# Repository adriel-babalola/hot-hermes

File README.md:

# Hot Hermes 🌡️

a mini temperature sensor + display for environment and room temperatures, with a buzzer that warns me when it gets above 34°C so i dont burn my food while cooking lol.

## Why i made this

i cook a lot and my kitchen gets HOT. i wanted something small that could just sit there, show me the temperature, and scream at me (well, buzz loudly) when things get too warm. also i wanted to finally learn how I2C works and this was the perfect excuse.

## How it works

- **AHT20 module** reads the temperature and humidity over I2C
- **1.3" OLED** displays the readings in real time
- **Passive buzzer** goes off when temp hits above 34°C
- everything runs on the **XIAO RP2040**
- Then there's a case, in which everything is enclosed in
## Screenshots

> 

## BOM

| Item # | Designator | Description | Qty | Unit Price (USD) | Total + Shipping (USD) | Source | Link |
|--------|------------|-------------|-----|-----------------|----------------------|--------|------|
| 1 | U1 | Seeed XIAO RP2040 Microcontroller | 1 | $7.84 | $7.84 | AliExpress | [link](https://www.aliexpress.com/item/1005006593701624.html?spm=a2g0o.cart.0.0.742b38daUU8kz0&mp=1&pdp_npi=6%40dis%21USD%21USD+6.31%21USD+4.61%21%21USD+4.61%21%21%21%40211b876717768556104776423e1131%2112000039072595754%21ct%21NG%216438462769%21%211%210%21&pdp_ext_f=%7B%22cart2PdpParams%22%3A%7B%22pdpBusinessMode%22%3A%22retail%22%7D%7D) |
| 2 | DS1 | 1.3" I2C OLED Display Module 128x64 (Blue) | 1 | $2.83| $2.83 | AliExpress | [link](https://www.aliexpress.com/item/1005010183965559.html?spm=a2g0o.cart.0.0.742b38daUU8kz0&mp=1&pdp_npi=6%40dis%21USD%21USD+8.28%21USD+3.89%21%21USD+3.85%21%21%21%40211b876717768556104776423e1131%2112000051437252682%21ct%21NG%216438462769%21%211%210%21) |
| 3 | U2 | AHT20 Temperature & Humidity Sensor Module | 1 | $2.06 | $2.06 | AliExpress | [link](https://www.aliexpress.com/item/1005006088708984.html?spm=a2g0o.cart.0.0.742b38daUU8kz0&mp=1&pdp_npi=6%40dis%21USD%21USD+2.16%21USD+2.16%21%21USD+2.12%21%21%21%40211b876717768556104776423e1131%2112000035679578526%21ct%21NG%216438462769%21%211%210%21) 
| 5 | PCB | hermes_Y5 Custom PCB — 5pcs, JLCPCB | 1 | $5.00 | $11.92 | PCBWAY | [link](https://pcbway.com) |
|6| 3D Printing | The Case for Hot Hermes | 1 | 0 | $9.39  | #printing-legion hackclub | - |
| | | | | **TOTAL** | **$34.02** | | |

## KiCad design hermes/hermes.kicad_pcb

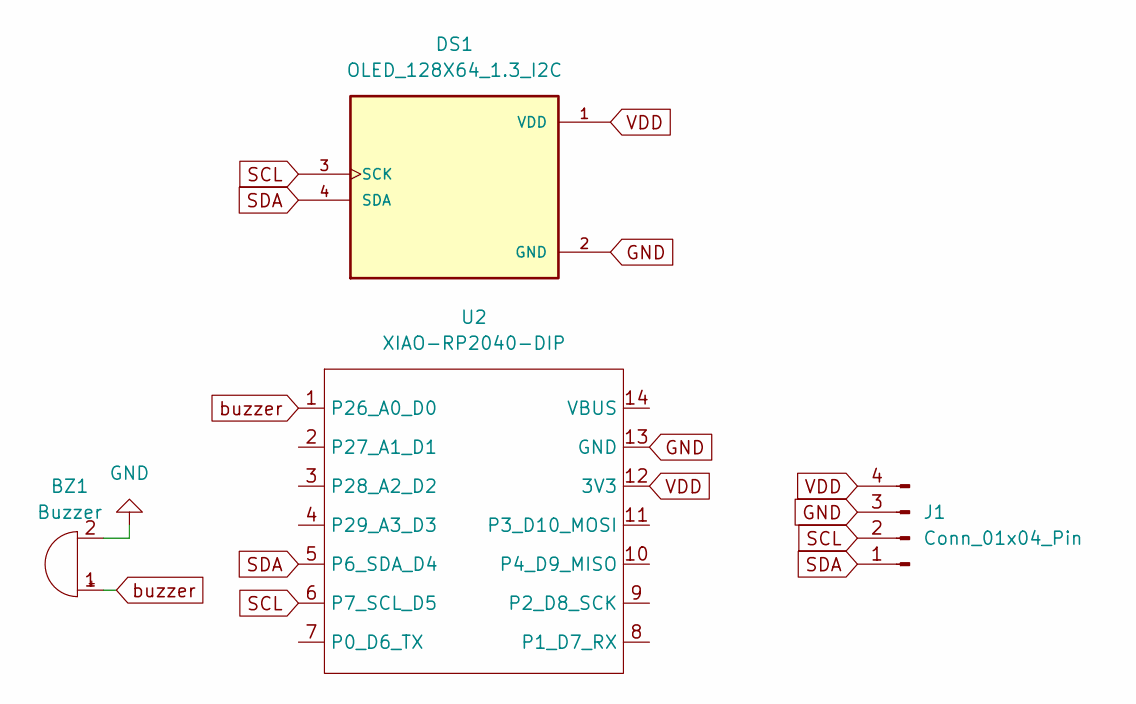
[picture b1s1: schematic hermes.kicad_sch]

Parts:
BZ1: Buzzer; Buzzer_12x9.5RM7.6
DS1: OLED_128X64_1.3_I2C; LCD_OLED_128X64_1.3_I2C; PARTREV NA
J1: Conn_01x04_Pin; FanPinHeader_1x04_P2.54mm_Vertical
U2: XIAO-RP2040-DIP

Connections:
GND: BZ1.2 (-), DS1.2 (GND), J1.3, U2.13 (GND)
SCL: DS1.3 (SCK), J1.2, U2.6 (P7_SCL_D5)
SDA: DS1.4 (SDA), J1.1, U2.5 (P6_SDA_D4)
VDD: DS1.1 (VDD), J1.4, U2.12 (3V3)
buzzer: BZ1.1 (+), U2.1 (P26_A0_D0)

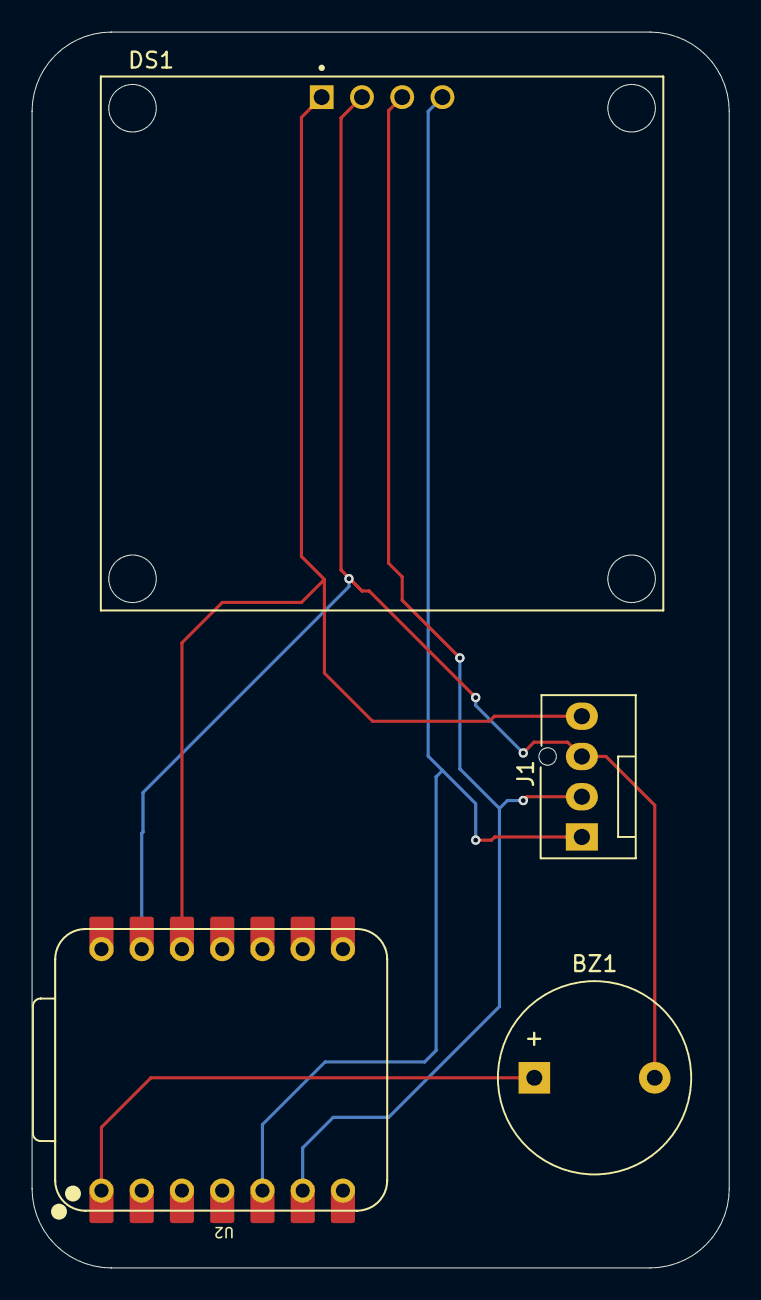
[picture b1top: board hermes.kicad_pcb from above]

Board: 2 copper layers, 44.0 x 78.0 mm, 4 parts (0 on the bottom side), 5 nets.

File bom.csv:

Item #,Designator,Description,Qty,Unit Price (USD),Total + Shipping (USD),Source,Link
1,U1,Seeed XIAO RP2040 Microcontroller,1,7.84,7.84,AliExpress,https://www.aliexpress.com/item/1005006593701624.html
2,DS1,"1.3"" I2C OLED Display Module 128x64 (Blue)",1,2.83,2.83,AliExpress,https://www.aliexpress.com/item/1005010183965559.html
3,U2,AHT20 Temperature & Humidity Sensor Module,1,2.06,2.06,AliExpress,https://www.aliexpress.com/item/1005006088708984.html
4,PCB,Hermes_Y5 Custom PCB — 5pcs,1,5,11.9,PCB Way,https://pcbway.com
5,CASE, #printing-legion hackclub,1,,9.39,,
,,,,TOTAL,34.02,,

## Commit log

2026-04-20 first-commit
2026-04-20 firmware complete
2026-04-21 changed some footprints
2026-04-22 done
2026-05-08 made a case
2026-05-10 done again
2026-05-11 done again again
